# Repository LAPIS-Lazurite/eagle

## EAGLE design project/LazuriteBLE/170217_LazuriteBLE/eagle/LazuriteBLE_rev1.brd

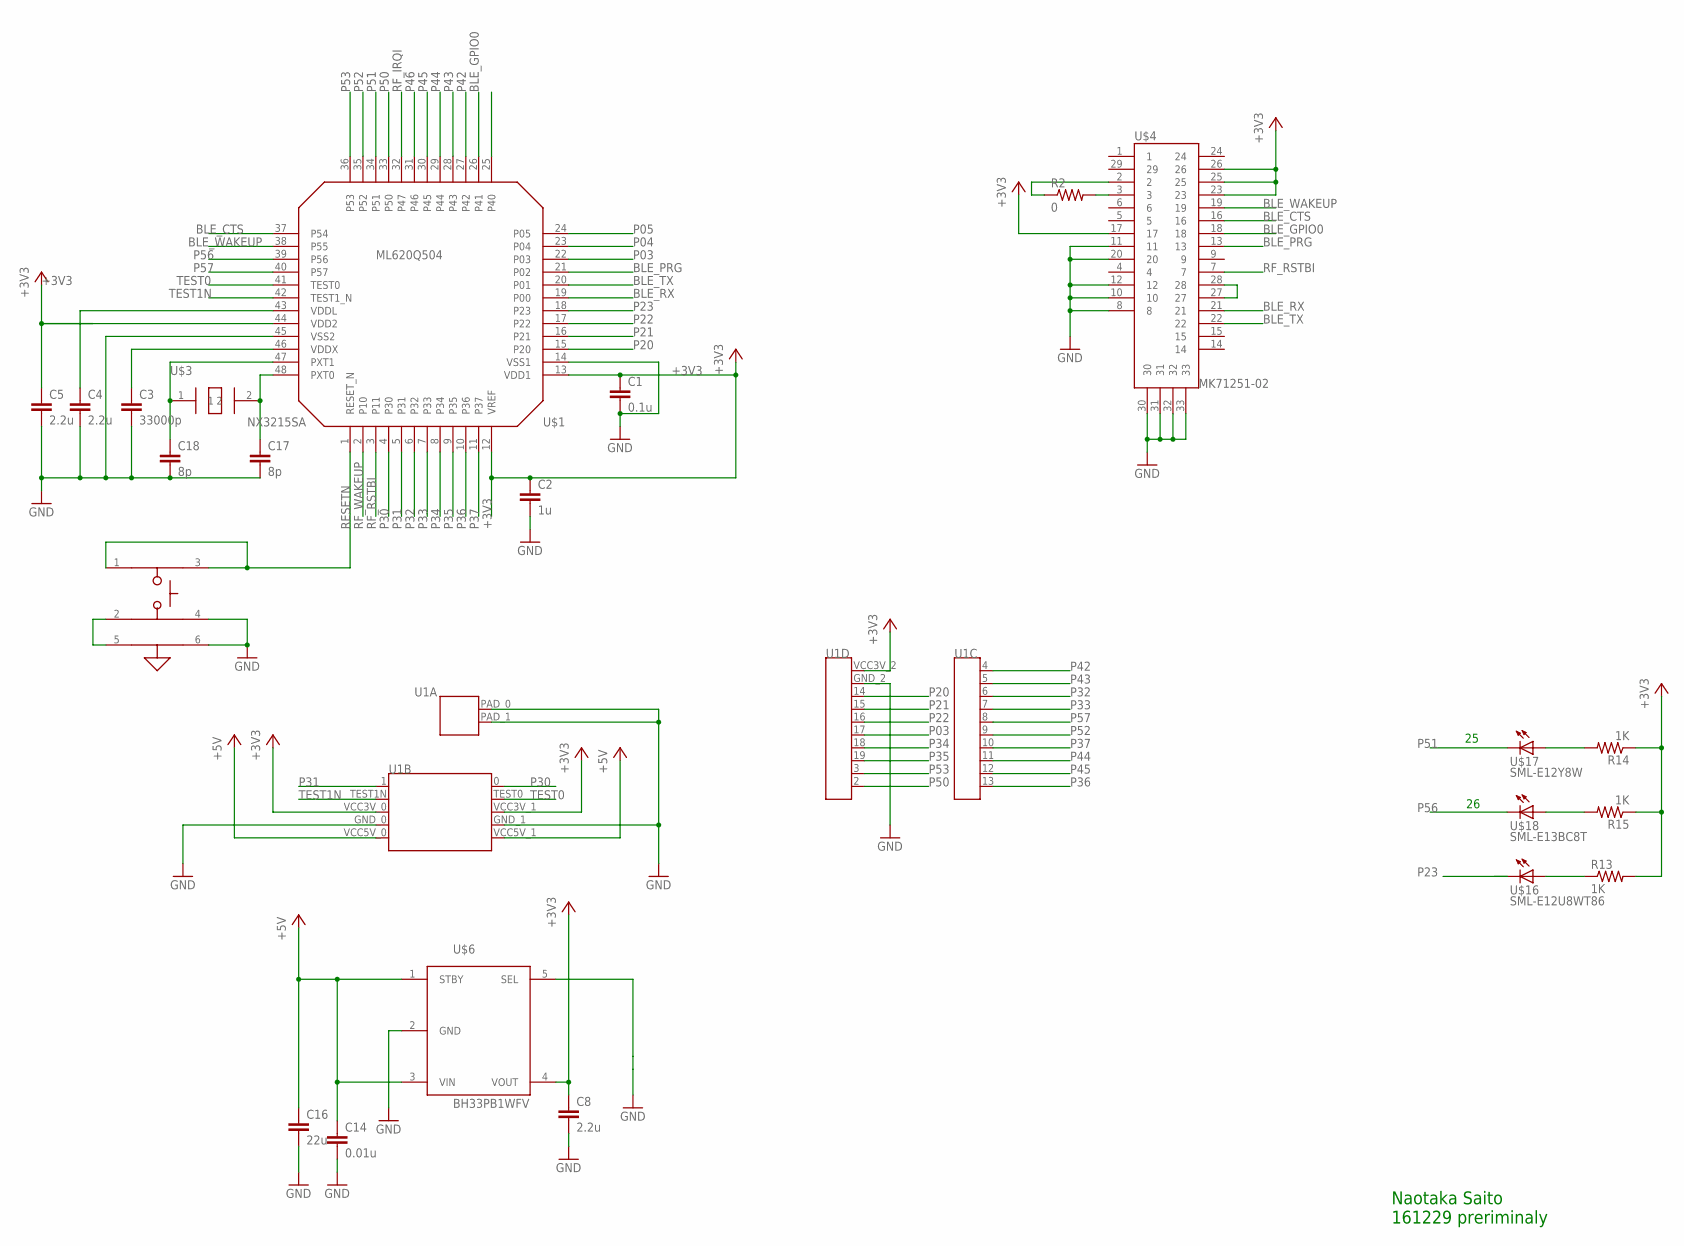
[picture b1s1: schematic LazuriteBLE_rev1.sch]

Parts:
C1: 0.1u; C0402
C2: 1u; C0402
C3: 33000p; C0402
C4, C5, C8: 2.2u; C0402
C14: 0.01u; C0402
C16: 22u; C1206
C17, C18: 8p; C0402
R2: 0; R0402
R13, R14, R15: 1K; R0402
SW1: SKSGACE010
U1: LAZURITE920J; LAZURITE920J2
U$1: ML620Q504
U$3: NX3215SA; NX3215SA-32,768K-SFD-MUA-14
U$4: MK71251-02
U$6: BH33PB1WFV; HVSOF5
U$16: SML-E12U8WT86; SML-E1X
U$17: SML-E12Y8W; SML-E1X
U$18: SML-E13BC8T; SML-E1X

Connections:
+3V3: C1.1, C2.1, C5.1, C8.1, R13.2, R14.1, R15.1, U1.VCC3V_0, U1.VCC3V_1, U1.VCC3V_2, U$1.12 (VREF), U$1.13 (VDD1), U$1.44 (VDD2), U$4.17, U$4.23, U$4.25, U$4.26, U$6.4 (VOUT)
+5V: C14.1, C16.1, U1.VCC5V_0, U1.VCC5V_1, U$6.1 (STBY), U$6.3 (VIN)
BLE_CTS: U$1.37 (P54), U$4.16
BLE_GPIO0: U$1.26 (P41), U$4.18
BLE_PRG: U$1.21 (P02), U$4.13
BLE_RX: U$1.19 (P00), U$4.21
BLE_TX: U$1.20 (P01), U$4.22
BLE_WAKEUP: U$1.38 (P55), U$4.19
GND: C1.2, C2.2, C3.2, C4.2, C5.2, C8.2, C14.2, C16.2, C17.2, C18.2, SW1.4, SW1.6, U1.GND_0, U1.GND_1, U1.GND_2, U1.PAD_0, U1.PAD_1, U$1.14 (VSS1), U$1.45 (VSS2), U$4.8, U$4.10, U$4.11, U$4.12, U$4.20, U$4.30, U$4.31, U$4.32, U$4.33, U$6.2 (GND), U$6.5 (SEL)
unnamed: C17.1, U$1.48 (PXT0), U$3.2
unnamed: C18.1, U$1.47 (PXT1), U$3.1
unnamed: C3.1, U$1.46 (VDDX)
unnamed: R2.2, U$4.3
unnamed: R14.2, U$17.A
unnamed: C4.1, U$1.43 (VDDL)
unnamed: R13.1, U$16.A
unnamed: R15.2, U$18.A
unnamed: R2.1, U$4.2
unnamed: U$4.27, U$4.28
unnamed: SW1.2, SW1.5
P03: U1.17, U$1.22 (P03)
P04: U$1.23 (P04)
P05: U$1.24 (P05)
P20: U1.14, U$1.15 (P20)
P21: U1.15, U$1.16 (P21)
P22: U1.16, U$1.17 (P22)
P23: U$1.18 (P23), U$16.C
P30: U1.0, U$1.4 (P30)
P31: U1.1, U$1.5 (P31)
P32: U1.6, U$1.6 (P32)
P33: U1.7, U$1.7 (P33)
P34: U1.18, U$1.8 (P34)
P35: U1.19, U$1.9 (P35)
P36: U1.13, U$1.10 (P36)
P37: U1.10, U$1.11 (P37)
P42: U1.4, U$1.27 (P42)
P43: U1.5, U$1.28 (P43)
P44: U1.11, U$1.29 (P44)
P45: U1.12, U$1.30 (P45)
P46: U$1.31 (P46)
P50: U1.2, U$1.33 (P50)
P51: U$1.34 (P51), U$17.C
P52: U1.9, U$1.35 (P52)
P53: U1.3, U$1.36 (P53)
P56: U$1.39 (P56), U$18.C
P57: U1.8, U$1.40 (P57)
RESETN: SW1.1, SW1.3, U$1.1 (RESET_N)
RF_IRQI: U$1.32 (P47)
RF_RSTBI: U$1.3 (P11), U$4.7
RF_WAKEUP: U$1.2 (P10)
SDA0I: U$1.25 (P40)
TEST0: U1.TEST0, U$1.41 (TEST0)
TEST1N: U1.TEST1N, U$1.42 (TEST1_N)

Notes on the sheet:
Naotaka Saito 161229 preriminaly

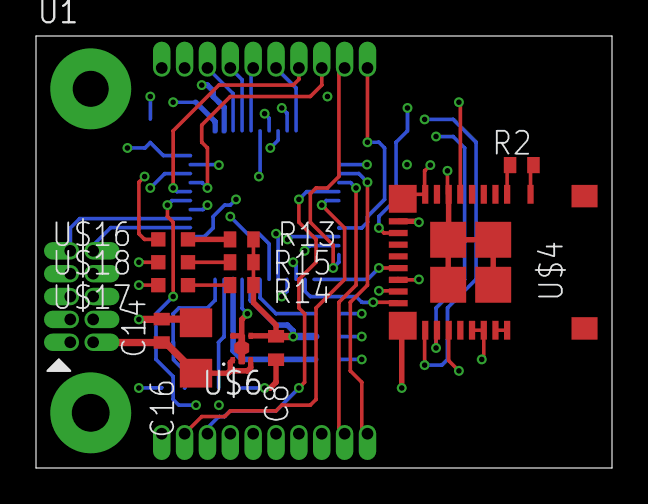
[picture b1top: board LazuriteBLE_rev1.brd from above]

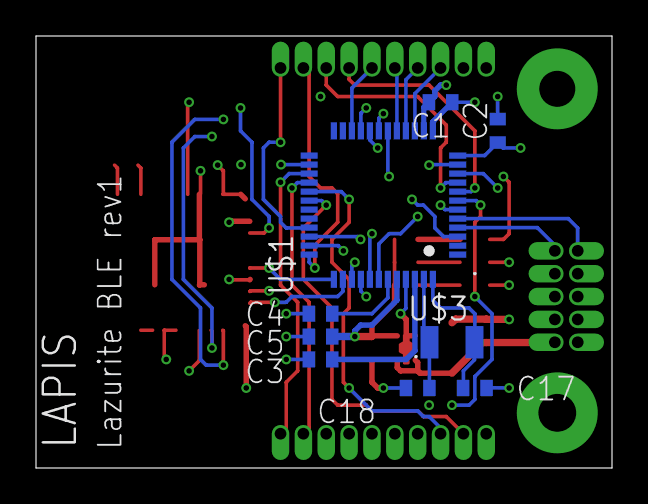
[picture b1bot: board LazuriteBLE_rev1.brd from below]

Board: 4 copper layers, 32.0 x 24.0 mm, 22 parts (9 on the bottom side), 45 nets.

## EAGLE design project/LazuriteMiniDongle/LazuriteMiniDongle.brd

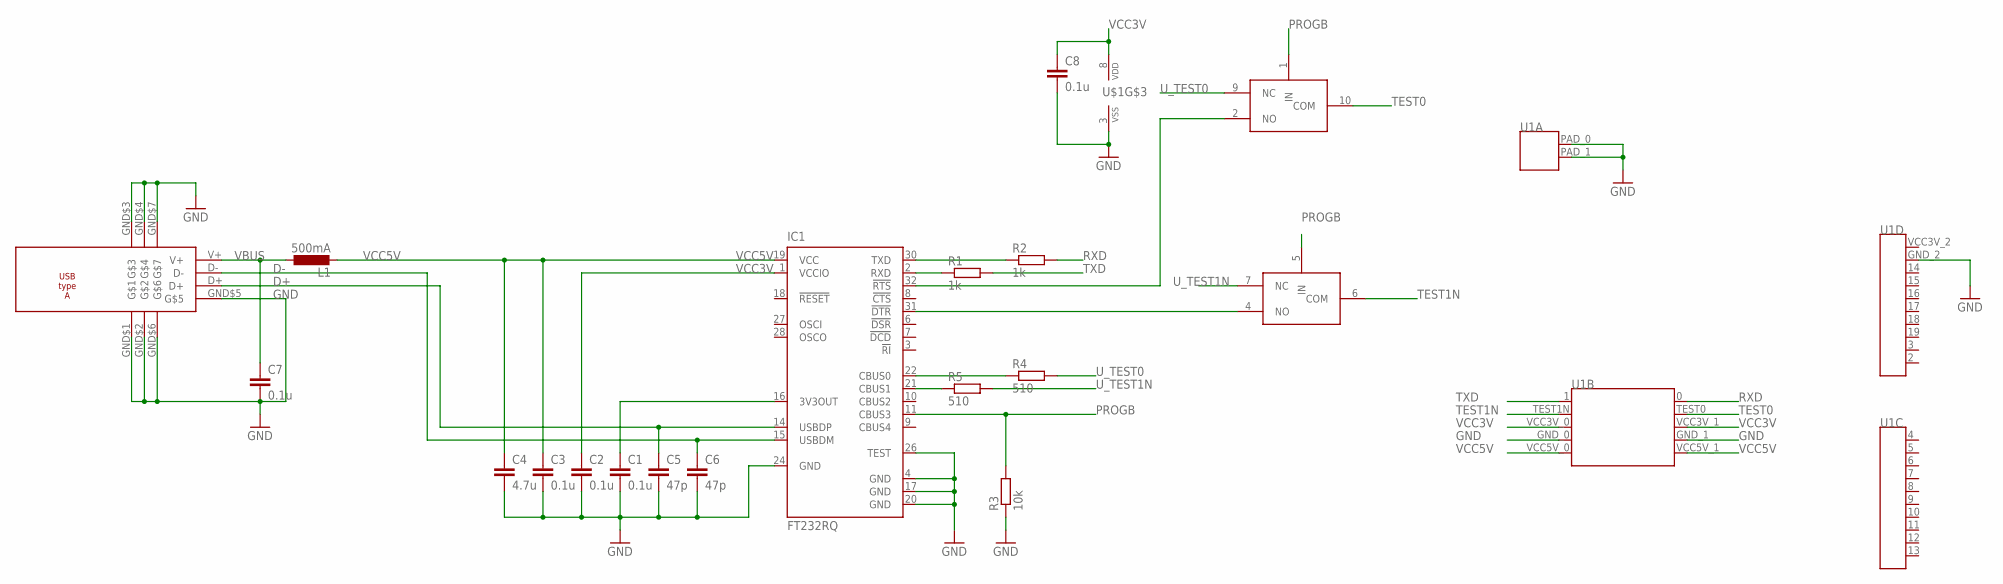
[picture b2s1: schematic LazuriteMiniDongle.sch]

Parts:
C1, C2, C3, C7, C8: 0.1u; C0402
C4: 4.7u; C1608
C5, C6: 47p; C0402
IC1: FT232RQ; QFN32
L1: 500mA; L1812
R1, R2: 1k; R0402
R3: 10k; R0402
R4, R5: 510; R0402
U1: LAZURITE920JLAZURITE920J; LAZURITE920J
U$1: TI-TS5A23159; UQFN10
U$2: USB-TYPE-A; UP2-AH-TH

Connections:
D+: C5.1, IC1.14 (USBDP), U$2.D+
D-: C6.1, IC1.15 (USBDM), U$2.D-
GND: C1.2, C2.2, C3.2, C4.2, C5.2, C6.2, C7.2, C8.2, IC1.4 (GND), IC1.17 (GND), IC1.20 (GND), IC1.24 (GND), IC1.26 (TEST), R3.1, U1.GND_0, U1.GND_1, U1.GND_2, U1.PAD_0, U1.PAD_1, U$1.3 (VSS), U$2.GND$1, U$2.GND$2, U$2.GND$3, U$2.GND$4, U$2.GND$5, U$2.GND$6, U$2.GND$7
unnamed: C1.1, IC1.16 (3V3OUT)
unnamed: IC1.32 (!RTS), U$1.2 (NO)
unnamed: IC1.2 (RXD), R1.1
unnamed: IC1.30 (TXD), R2.1
unnamed: IC1.21 (CBUS1), R5.1
unnamed: IC1.22 (CBUS0), R4.1
unnamed: IC1.31 (!DTR), U$1.4 (NO)
PROGB: IC1.11 (CBUS3), R3.2, U$1.1 (IN), U$1.5 (IN)
RXD: R2.2, U1.0
TEST0: U1.TEST0, U$1.10 (COM)
TEST1N: U1.TEST1N, U$1.6 (COM)
TXD: R1.2, U1.1
U_TEST0: R4.2, U$1.9 (NC)
U_TEST1N: R5.2, U$1.7 (NC)
VBUS: C7.1, L1.1, U$2.V+
VCC3V: C2.1, C8.1, IC1.1 (VCCIO), U1.VCC3V_0, U1.VCC3V_1, U$1.8 (VDD)
VCC5V: C3.1, C4.1, IC1.19 (VCC), L1.2, U1.VCC5V_0, U1.VCC5V_1

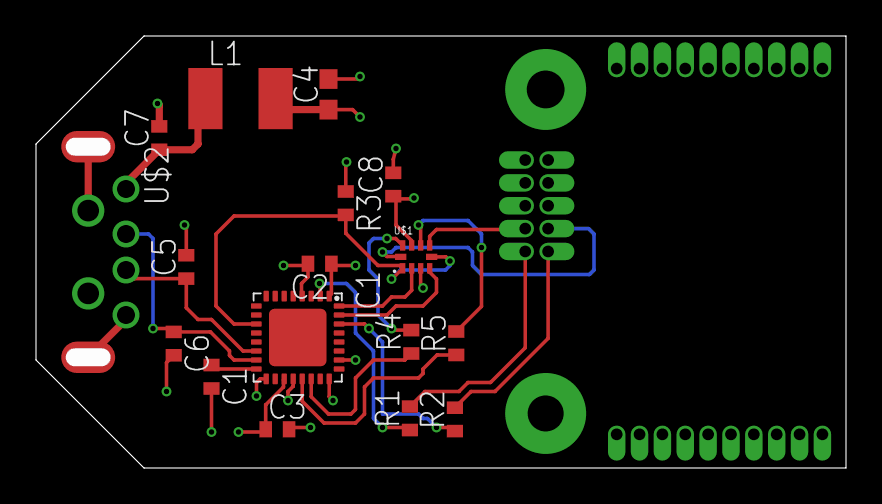
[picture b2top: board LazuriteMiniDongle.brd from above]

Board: 4 copper layers, 45.0 x 24.0 mm, 18 parts (1 on the bottom side), 20 nets.
